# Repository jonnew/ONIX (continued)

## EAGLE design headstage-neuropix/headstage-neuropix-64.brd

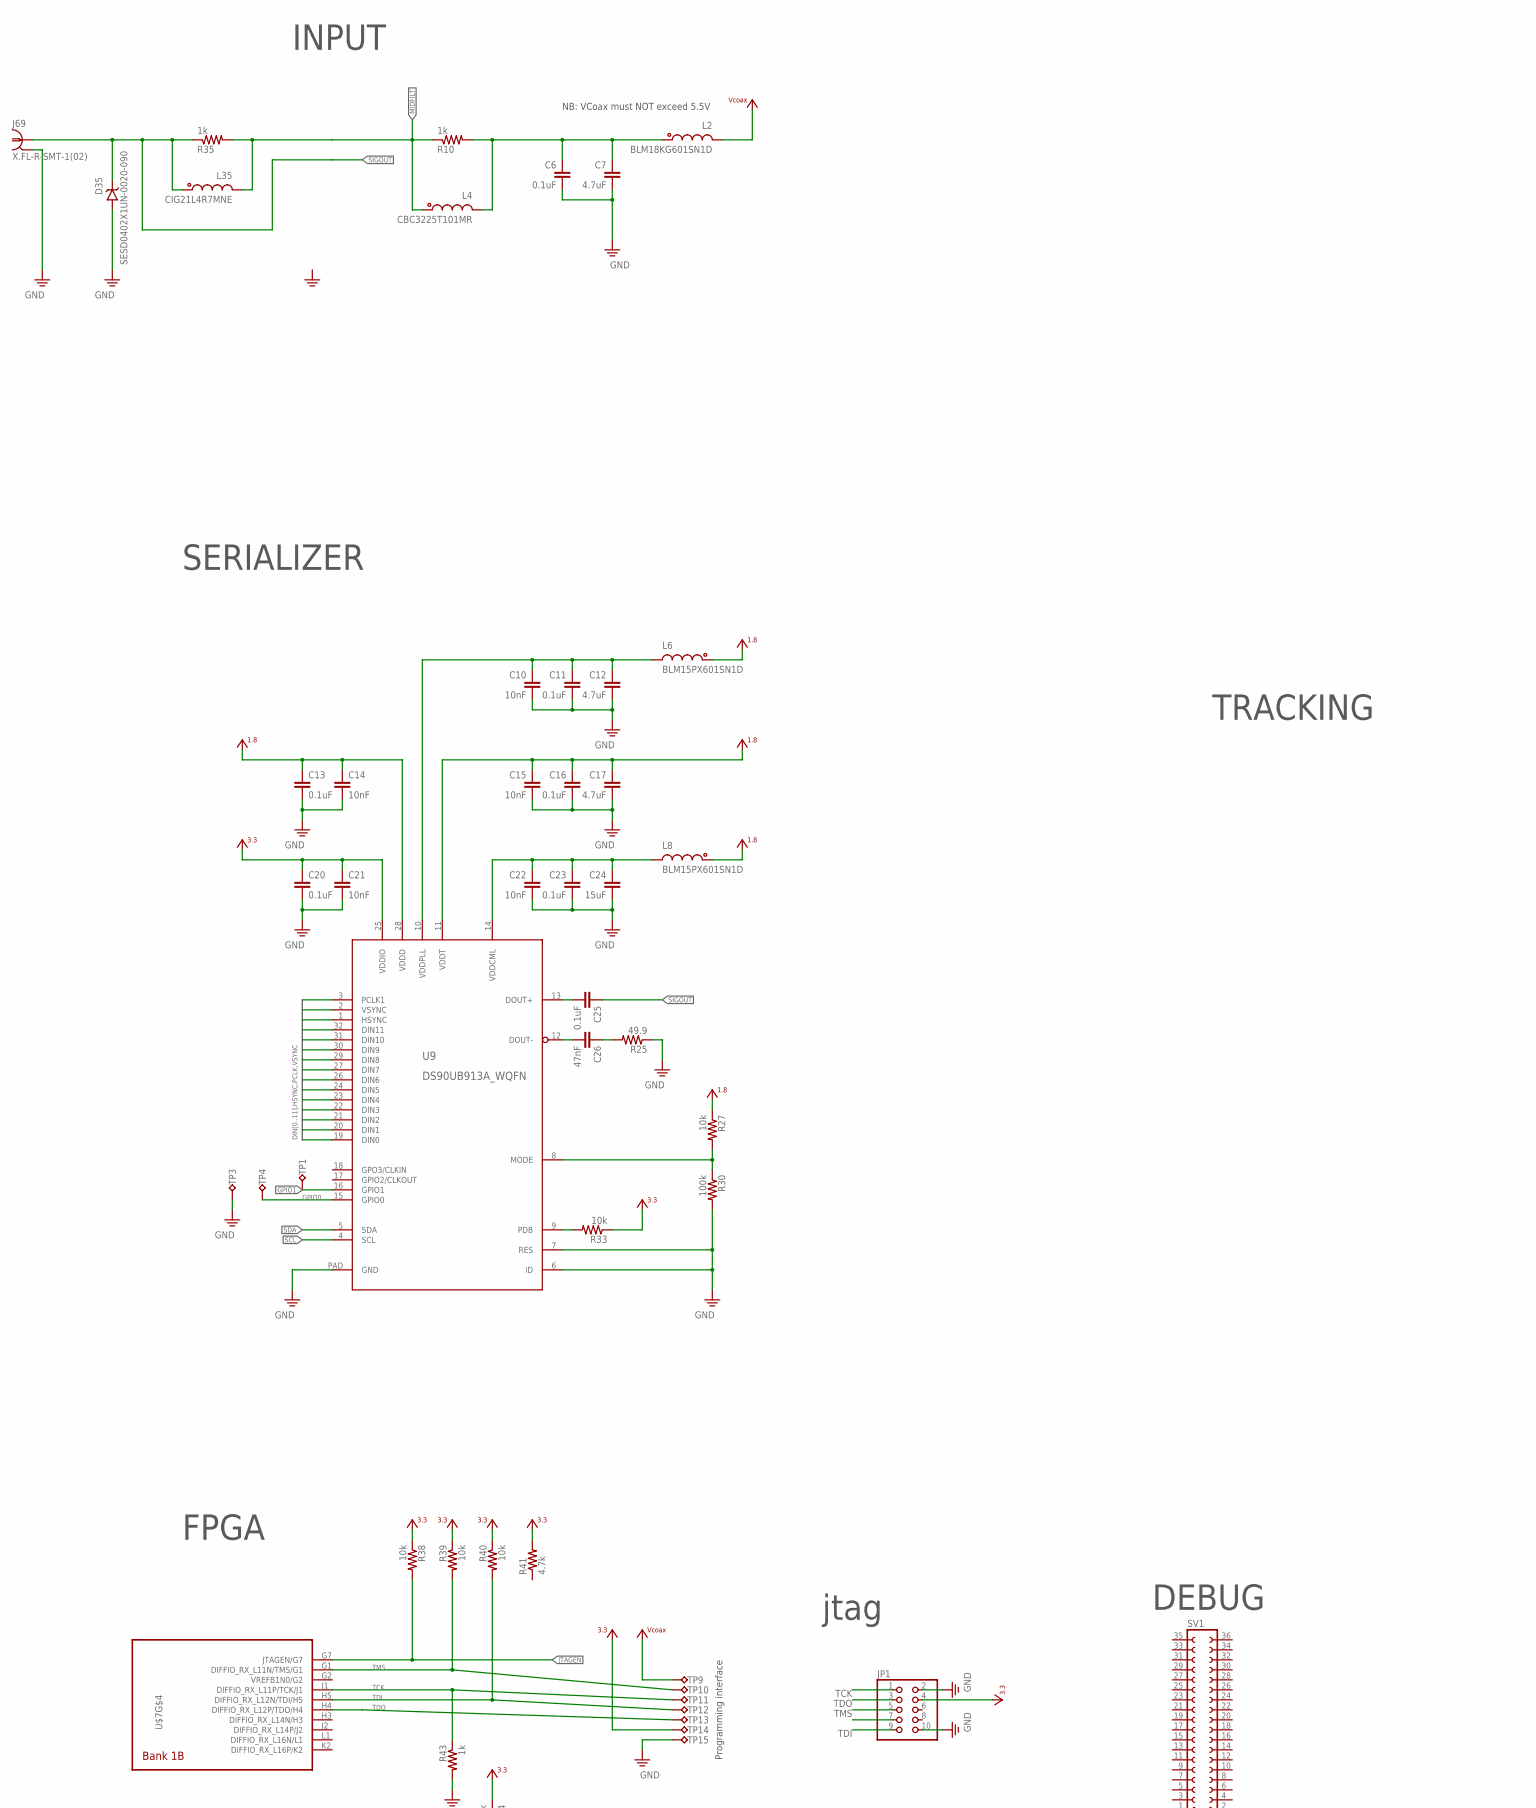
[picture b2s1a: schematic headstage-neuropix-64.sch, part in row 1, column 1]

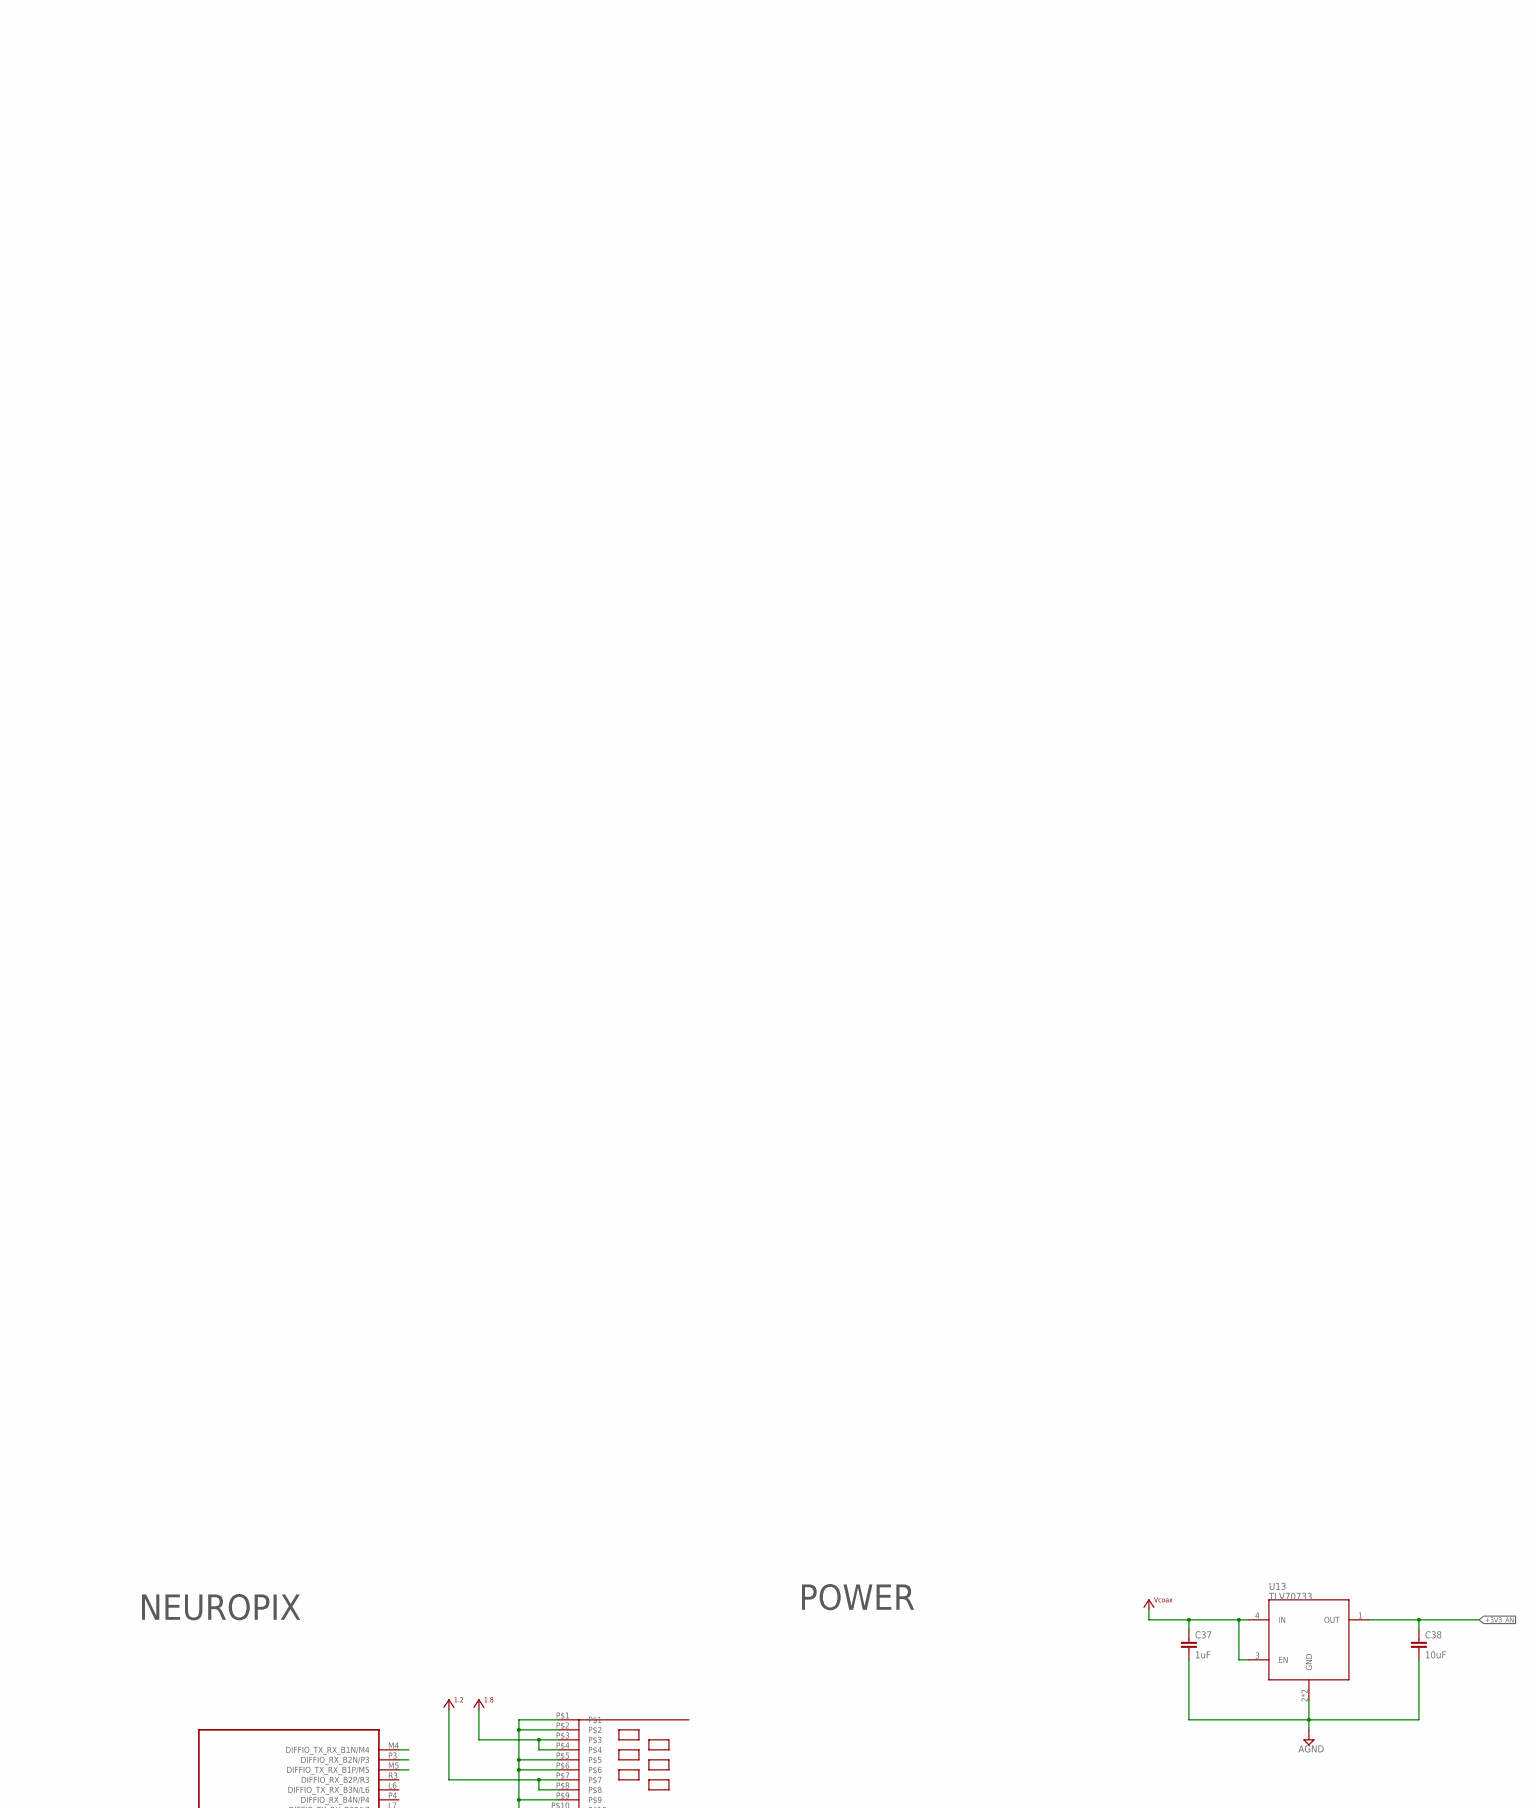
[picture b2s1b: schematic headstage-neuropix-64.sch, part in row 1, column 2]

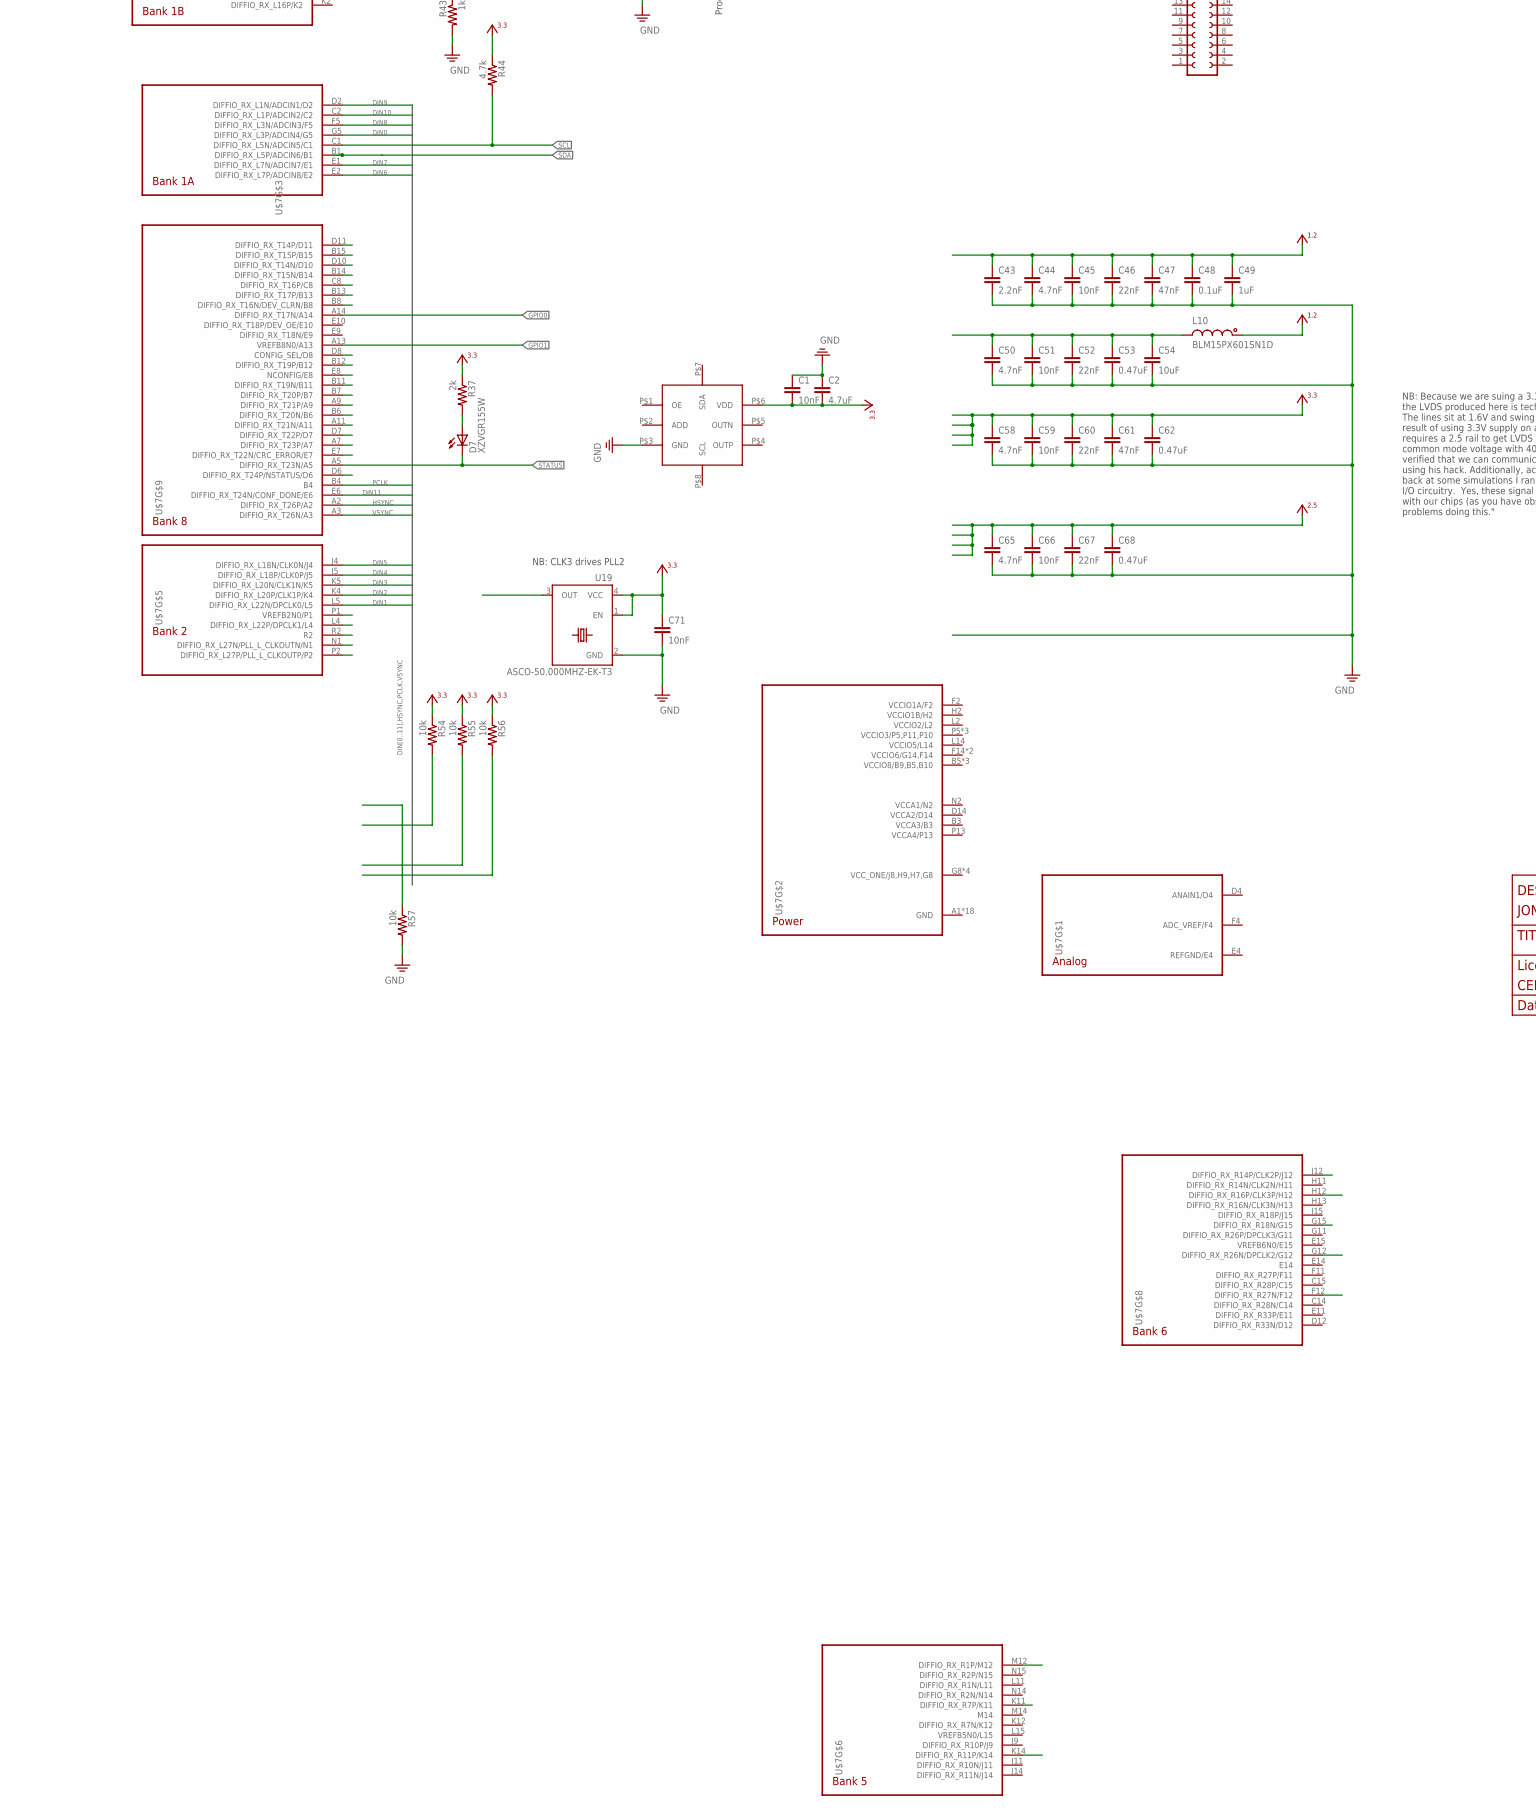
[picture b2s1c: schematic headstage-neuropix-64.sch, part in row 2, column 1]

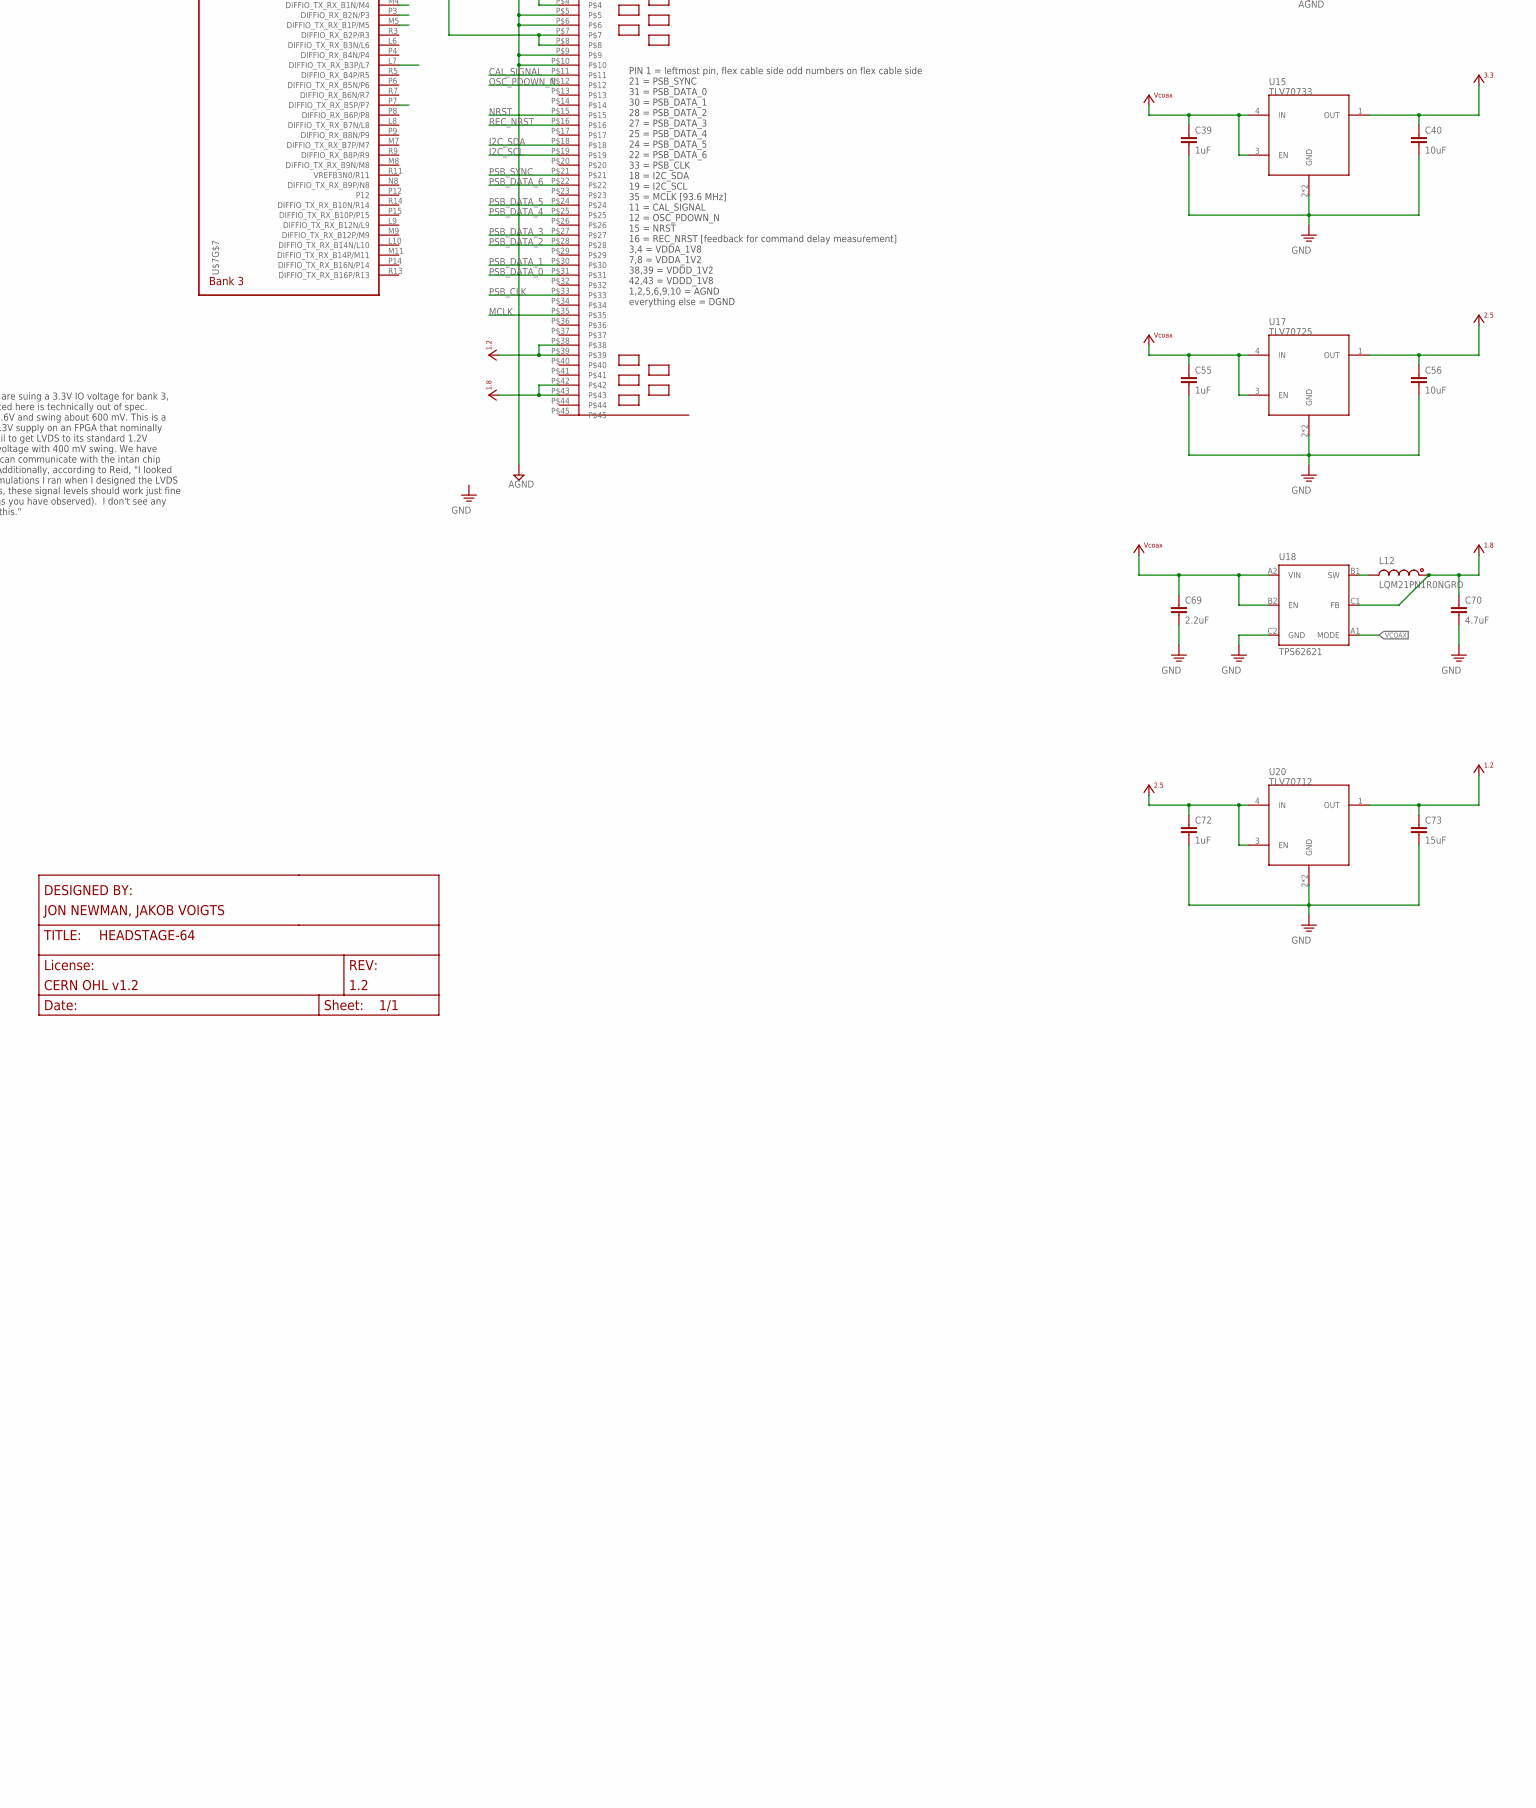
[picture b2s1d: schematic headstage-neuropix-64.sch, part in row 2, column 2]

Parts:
C1, C10, C14, C15, C21, C22, C45, C51, C59, C66, C71: 10nF; 0201T
C2, C70: 4.7uF; 0402T; PARTNO CL05A105KO5NNNC
C6: 0.1uF; 0201T; PARTNO C0603X5R1C104K030BC
C7: 4.7uF; 0402T; PARTNO CL05A475MO5NUNC
C11, C13, C16, C20, C23, C48: 0.1uF; 0201T
C12, C17: 4.7uF; 0402T; PARTNO GRM155R61A475MEAAD
C24: 15uF; 0402T; PARTNO CL05A226MQ5QUNC
C25: 0.1uF; 0201T; PARTNO C1005X7R1H104K050BB
C26: 47nF; 0201T; PARTNO C1005X7R1H473K050BB
C37, C39, C55, C72: 1uF; 0402T; PARTNO CL05A105KO5NNNC
C38, C40, C54, C56: 10uF; 0402T; PARTNO CL05A106MQ5NUNC
C43: 2.2nF; 0201T
C44, C50, C58, C65: 4.7nF; 0201T
C46, C52, C60, C67: 22nF; 0201T
C47, C61: 47nF; 0201T
C49: 1uF; 0201T; PARTNO CL03A105MP3ZSNH
C53, C62, C68: 0.47uF; 0201T; PARTNO GRM033R60J474KE90D
C69: 2.2uF; 0402T; PARTNO CL05A105KO5NNNC
C73: 15uF; 0402T; PARTNO CL05A226MQ6ZUN8
D7: XZVGR155W; LED-0201T
D35: SESD0402X1UN-0020-090; 0402T-DFN
J69: X.FL-R-SMT-1(02); X_FL_R_SMT_1(02)
JP1: PINHD-2X5; 2X05
L2: BLM18KG601SN1D; 0603T
L4: CBC3225T101MR; 1210T
L6, L8, L10: BLM15PX601SN1D; 0402T; PARTNO BLM15PX601SN1D
L12: LQM21PN1R0NGRD; 0805T
L35: CIG21L4R7MNE; 0805T
R10, R35, R43: 1k; 0201T
R25: 49.9; 0201T
R27, R33, R38, R39, R40, R54, R55, R56, R57: 10k; 0201T
R30: 100k; 0201T
R37: 2k; 0201T
R41, R44: 4.7k; 0201T
SV1: FE18-2
TP1, TP3, TP4: TPTP09R; TP09R
TP9, TP10, TP11, TP12, TP13: TPTP06R; TP06R
TP14: gnd; TP06R
TP15: VCC; TP06R
U9: DS90UB913A_WQFN; WQFN32-5X5
U13, U15: TLV70733; X2SON
U17: TLV70725; X2SON
U18: TPS62621; XBGA6_1.2X0.8
U19: ASCO-50.000MHZ-EK-T3; ASCO
U20: TLV70712; X2SON
U$2: CONNFPCBOTTOM45POS0.30MMR/A; FH23-45S-0.3SHW(05)
U$3: LMK61E2; QFM8
U$7: 10M08SAM153_MBGA; MBGA153-8X8

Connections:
$N324: C50.1, C51.1, C52.1, C53.1, C54.1, L10.2
+1V2: C43.1, C44.1, C45.1, C46.1, C47.1, C48.1, C49.1, C73.1, L10.1, U20.1 (OUT), U$2.P$7, U$2.P$8, U$2.P$38, U$2.P$39
+1V8: C13.1, C14.1, C15.1, C16.1, C17.1, C70.1, L6.1, L8.1, L12.1, R27.1, U9.11 (VDDT), U9.28 (VDDD), U18.C1 (FB), U$2.P$3, U$2.P$4, U$2.P$42, U$2.P$43
+2V5: C56.1, C65.1, C66.1, C67.1, C68.1, C72.1, U17.1 (OUT), U20.3 (EN), U20.4 (IN)
+3V3: C1.2, C2.2, C20.1, C21.1, C40.1, C58.1, C59.1, C60.1, C61.1, C62.1, C71.1, JP1.4, R33.1, R37.1, R38.1, R39.1, R40.1, R41.2, R44.1, R54.1, R55.1, R56.1, TP14.TP, U9.25 (VDDIO), U15.1 (OUT), U19.1 (EN), U19.4 (VCC), U$3.P$6 (VDD)
+3V3_AN: C38.1, U13.1 (OUT)
AGND: C37.2, C38.2, U13.2 (GND), U13.PAD (GND), U$2.P$1, U$2.P$2, U$2.P$5, U$2.P$6, U$2.P$9, U$2.P$10
CAL_SIGNAL: U$2.P$11
CONFIG_SEL: R57.1
CONF_DONE: R56.2
DIN0: U9.19 (DIN0), U$7.G5 (DIFFIO_RX_L3P/ADCIN4/G5)
DIN1: U9.20 (DIN1), U$7.L5 (DIFFIO_RX_L22N/DPCLK0/L5)
DIN2: U9.21 (DIN2), U$7.K4 (DIFFIO_RX_L20P/CLK1P/K4)
DIN3: U9.22 (DIN3), U$7.K5 (DIFFIO_RX_L20N/CLK1N/K5)
DIN4: U9.23 (DIN4), U$7.J5 (DIFFIO_RX_L18P/CLK0P/J5)
DIN5: U9.24 (DIN5), U$7.J4 (DIFFIO_RX_L18N/CLK0N/J4)
DIN6: U9.26 (DIN6), U$7.E2 (DIFFIO_RX_L7P/ADCIN8/E2)
DIN7: U9.27 (DIN7), U$7.E1 (DIFFIO_RX_L7N/ADCIN7/E1)
DIN8: U9.29 (DIN8), U$7.F5 (DIFFIO_RX_L3N/ADCIN3/F5)
DIN9: U9.30 (DIN9), U$7.D2 (DIFFIO_RX_L1N/ADCIN1/D2)
DIN10: U9.31 (DIN10), U$7.C2 (DIFFIO_RX_L1P/ADCIN2/C2)
DIN11: U9.32 (DIN11), U$7.E6 (DIFFIO_RX_T24N/CONF_DONE/E6)
GND: C1.1, C2.1, C6.2, C7.2, C10.2, C11.2, C12.2, C13.2, C14.2, C15.2, C16.2, C17.2, C20.2, C21.2, C22.2, C23.2, C24.2, C39.2, C40.2, C43.2, C44.2, C45.2, C46.2, C47.2, C48.2, C49.2, C50.2, C51.2, C52.2, C53.2, C54.2, C55.2, C56.2, C58.2, C59.2, C60.2, C61.2, C62.2, C65.2, C66.2, C67.2, C68.2, C69.2, C70.2, C71.2, C72.2, C73.2, D35.A, J69.P$2 (2), J69.P$3 (2), J69.P$4 (2), JP1.2, JP1.10, R25.1, R30.2, R43.2, R57.2, TP3.TP, TP15.TP, U9.6 (ID), U9.7 (RES), U9.PAD (GND), U15.2 (GND), U15.PAD (GND), U17.2 (GND), U17.PAD (GND), U18.C2 (GND), U19.2 (GND), U20.2 (GND), U20.PAD (GND), U$3.P$3 (GND), U$7.A1 (GND), U$7.A15 (GND), U$7.B2 (GND), U$7.D5 (GND), U$7.D9 (GND), U$7.E5 (GND), U$7.E12 (GND), U$7.G4 (GND), U$7.G9 (GND), U$7.H8 (GND), U$7.H14 (GND), U$7.J7 (GND), U$7.L12 (GND), U$7.M2 (GND), U$7.M6 (GND), U$7.M10 (GND), U$7.R1 (GND), U$7.R15 (GND)
GPIO0: TP4.TP, U9.15 (GPIO0), U$7.A14 (DIFFIO_RX_T17N/A14)
GPIO1: TP1.TP, U9.16 (GPIO1), U$7.A13 (VREFB8N0/A13)
HSYNC: U9.1 (HSYNC), U$7.A2 (DIFFIO_RX_T26P/A2)
I2C_SCL: U$2.P$19
I2C_SDA: U$2.P$18
JTAGEN: R38.2, U$7.G7 (JTAGEN/G7)
MCLK: U$2.P$35
MIDFILT: L4.1, L35.2, R10.1, R35.2
unnamed: C6.1, C7.1, L2.1, L4.2, R10.2
unnamed: C25.2, U9.13 (DOUT+)
unnamed: D7.2 (A), R37.2
unnamed: R33.2, U9.9 (PDB)
unnamed: C26.2, U9.12 (DOUT-)
unnamed: C26.1, R25.2
unnamed: R27.2, R30.1, U9.8 (MODE)
unnamed: C10.1, C11.1, C12.1, L6.2, U9.10 (VDDPLL)
unnamed: C22.1, C23.1, C24.1, L8.2, U9.14 (VDDCML)
unnamed: L12.2, U18.B1 (SW)
NRST: U$2.P$15
NSTATUS: R55.2
OSC_PDOWN_N: U$2.P$12
PCLK: U9.3 (PCLK1), U$7.B4
PSB_CLK: U$2.P$33
PSB_DATA_0: U$2.P$31
PSB_DATA_1: U$2.P$30
PSB_DATA_2: U$2.P$28
PSB_DATA_3: U$2.P$27
PSB_DATA_4: U$2.P$25
PSB_DATA_5: U$2.P$24
PSB_DATA_6: U$2.P$22
PSB_SYNC: U$2.P$21
REC_NRST: U$2.P$16
REFGND/E4: U$7.E4 (REFGND/E4)
SCL: R44.2, U9.4 (SCL), U$7.C1 (DIFFIO_RX_L5N/ADCIN5/C1)
SDA: U9.5 (SDA), U$7.B1 (DIFFIO_RX_L5P/ADCIN6/B1)
SIGOUT: C25.1, D35.C, J69.P$1 (1), L35.1, R35.1
STATUS: D7.1 (C), U$7.A5 (DIFFIO_RX_T23N/A5)
TCK: JP1.1, R43.1, TP11.TP, U$7.J1 (DIFFIO_RX_L11P/TCK/J1)
TDI: JP1.9, R40.2, TP12.TP, U$7.H5 (DIFFIO_RX_L12N/TDI/H5)
TDO: JP1.3, TP13.TP, U$7.H4 (DIFFIO_RX_L12P/TDO/H4)
TMS: JP1.5, R39.2, TP10.TP, U$7.G1 (DIFFIO_RX_L11N/TMS/G1)
VCCA1/N2: U$7.N2 (VCCA1/N2)
VCCA2/D14: U$7.D14 (VCCA2/D14)
VCCA3/B3: U$7.B3 (VCCA3/B3)
VCCA4/P13: U$7.P13 (VCCA4/P13)
VCCIO1A/F2: U$7.F2 (VCCIO1A/F2)
VCCIO1B/H2: U$7.H2 (VCCIO1B/H2)
VCCIO2/L2: U$7.L2 (VCCIO2/L2)
VCCIO3/P5,P11,P10: U$7.P5 (VCCIO3/P5,P11,P10), U$7.P10 (VCCIO3/P5,P11,P10), U$7.P11 (VCCIO3/P5,P11,P10)
VCCIO5/L14: U$7.L14 (VCCIO5/L14)
VCCIO6/G14,F14: U$7.F14 (VCCIO6/G14,F14), U$7.G14 (VCCIO6/G14,F14)
VCCIO8/B9,B5,B10: U$7.B5 (VCCIO8/B9,B5,B10), U$7.B9 (VCCIO8/B9,B5,B10), U$7.B10 (VCCIO8/B9,B5,B10)
VCC_ONE/J8,H9,H7,G8: U$7.G8 (VCC_ONE/J8,H9,H7,G8), U$7.H7 (VCC_ONE/J8,H9,H7,G8), U$7.H9 (VCC_ONE/J8,H9,H7,G8), U$7.J8 (VCC_ONE/J8,H9,H7,G8)
VCOAX: C37.1, C39.1, C55.1, C69.1, L2.2, TP9.TP, U13.3 (EN), U13.4 (IN), U15.3 (EN), U15.4 (IN), U17.3 (EN), U17.4 (IN), U18.A1 (MODE), U18.A2 (VIN), U18.B2 (EN)
VSYNC: U9.2 (VSYNC), U$7.A3 (DIFFIO_RX_T26N/A3)

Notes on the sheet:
NB: VCoax must NOT exceed 5.5V
Programming interface
INPUT
SERIALIZER
FPGA
TRACKING
POWER
NB: Because we are suing a 3.3V IO voltage for bank 3, the LVDS produced here is technically out of spec. The lines sit at 1.6V and swing about 600 mV. This is a result of using 3.3V supply on an FPGA that nominally requires a 2.5 rail to get LVDS to its standard 1.2V common mode voltage with 400 m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
NB: CLK3 drives PLL2
NEUROPIX
DEBUG
jtag
PIN 1 = leftmost pin, flex cable side odd numbers on flex cable side 21 = PSB_SYNC 31 = PSB_DATA_0 30 = PSB_DATA_1 28 = PSB_DATA_2 27 = PSB_DATA_3 25 = PSB_DATA_4 24 = PSB_DATA_5 22 = PSB_DATA_6 33 = PSB_CLK 18 = I2C_SDA 19 = I2C_SCL 35 = MCLK [93.6 MHz] 11 = CAL_SIGNAL 12 = OSC_PDOWN_N 15 = NRST 1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

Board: 2 copper layers, 100 parts (61 on the bottom side), 50 nets, no tracks yet.
